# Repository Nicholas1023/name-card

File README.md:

# My PCB Name Card
My PCB name card has a microcontroller that lights 2 LEDs as it's output. It also has wireless capabilities on it. The card uses a 3V CR2032 battery to power it.

## Schematic

## PCB

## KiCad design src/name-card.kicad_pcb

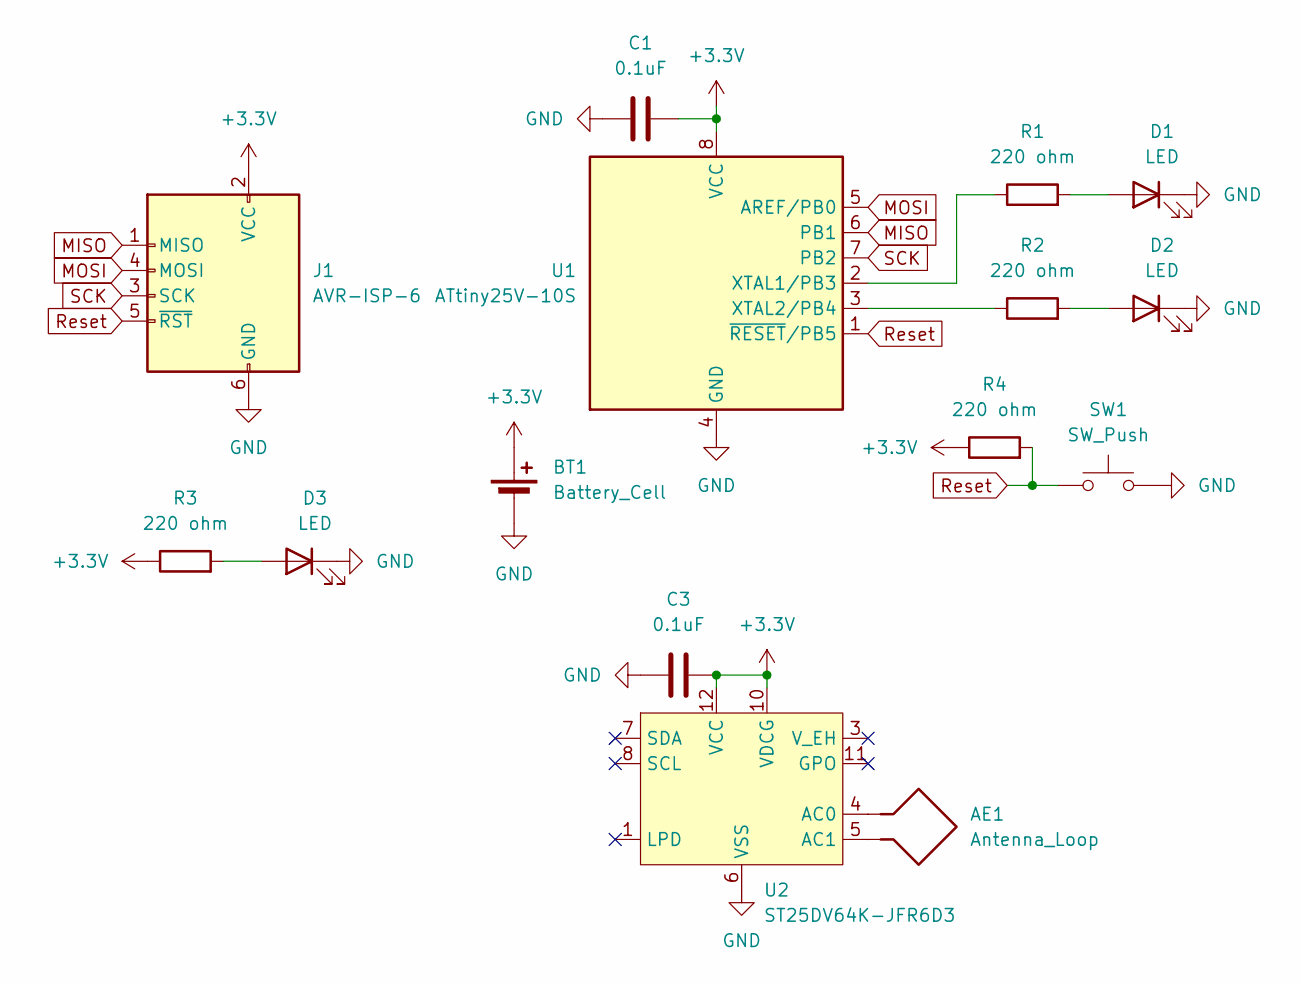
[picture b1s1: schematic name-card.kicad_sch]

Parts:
AE1: Antenna_Loop; NFC Coil
BT1: Battery_Cell; BatteryHolder_Keystone_3034_1x20mm
C1, C3: 0.1uF; C_0402_1005Metric; LCSC C1581
D1, D2, D3: LED; LED_0603_1608Metric; LCSC C2286
J1: AVR-ISP-6; PinHeader_2x03_P2.54mm_Vertical
R1, R2, R3, R4: 220 ohm; R_0402_1005Metric; LCSC C25091
SW1: SW_Push; SW_PUSH_6mm
U1: ATtiny25V-10S; SOIC-8_5.3x5.3mm_P1.27mm; LCSC C139660
U2: ST25DV64K-JFR6D3; ST_UFDFPN-12-1EP_3x3mm_P0.5mm_EP1.4x2.55mm; LCSC C5267460

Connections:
+3.3V: BT1.1 (+), C1.1, C3.1, J1.2 (VCC), R3.1, R4.1, U1.8 (VCC), U2.10 (VDCG), U2.12 (VCC)
GND: BT1.2 (-), C1.2, C3.2, D1.1 (K), D2.1 (K), D3.1 (K), J1.6 (GND), SW1.2, U1.4 (GND), U2.6 (VSS)
MISO: J1.1 (MISO), U1.6 (PB1)
MOSI: J1.4 (MOSI), U1.5 (AREF/PB0)
unnamed: D1.2 (A), R1.2
unnamed: D2.2 (A), R2.2
unnamed: D3.2 (A), R3.2
unnamed: R1.1, U1.2 (XTAL1/PB3)
unnamed: R2.1, U1.3 (XTAL2/PB4)
unnamed: AE1.1, U2.4 (AC0)
unnamed: AE1.2, U2.5 (AC1)
Reset: J1.5 (~RST), R4.2, SW1.1, U1.1 (~RESET/PB5)
SCK: J1.3 (SCK), U1.7 (PB2)

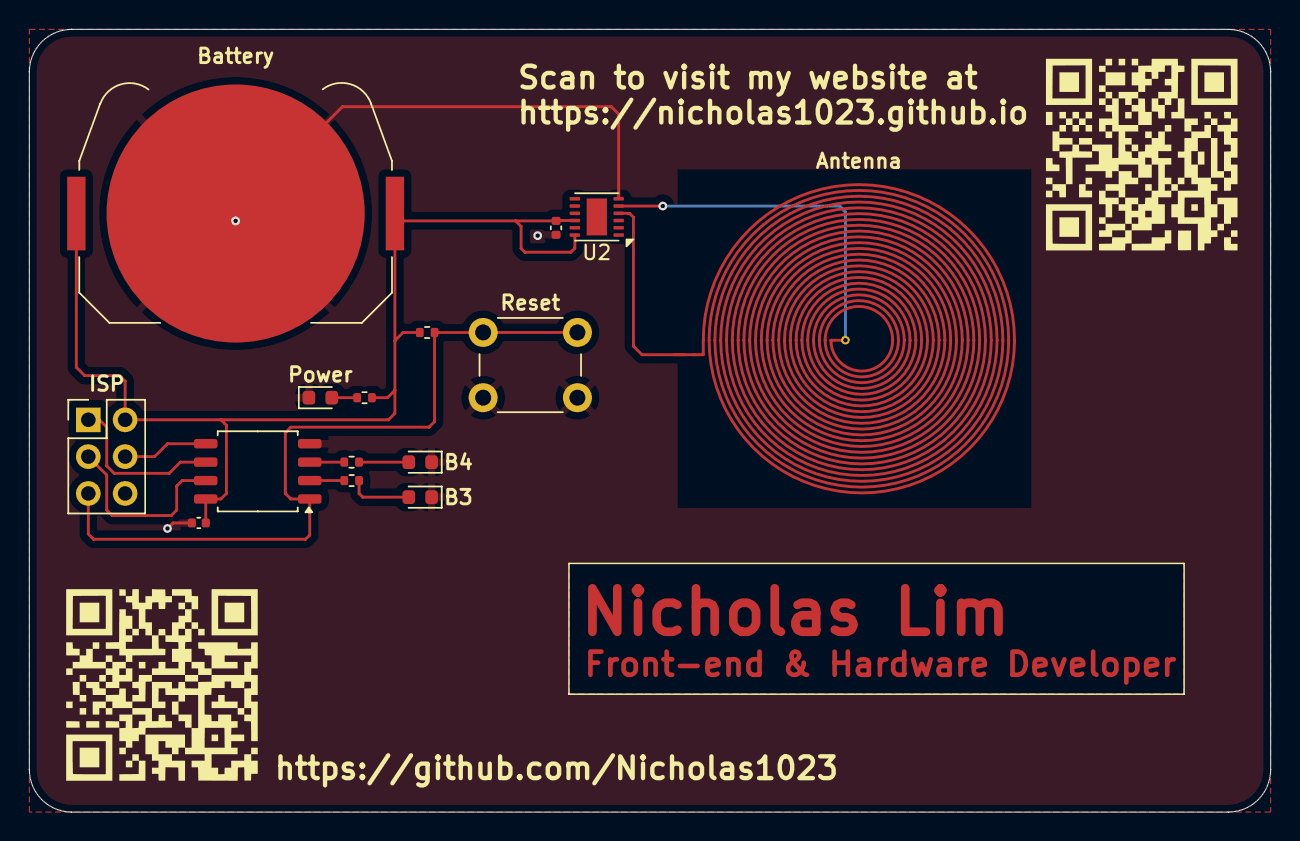
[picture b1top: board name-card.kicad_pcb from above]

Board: 2 copper layers, 85.6 x 54.0 mm, 15 parts (0 on the bottom side), 13 nets.

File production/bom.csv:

Designator,Footprint,Quantity,Value,LCSC Part #
"C1, C3",0402,2,0.1uF,C1581
"D1, D2, D3",0603,3,LED,C2286
J1,PinHeader_2x03_P2.54mm_Vertical,1,AVR-ISP-6,C65114
"R1, R2, R3, R4",0402,4,220 ohm,C25091
U1,SOIC-8_5.3x5.3mm_P1.27mm,1,ATtiny25V-10S,C139660
U2,ST_UFDFPN-12-1EP_3x3mm_P0.5mm_EP1.4x2.55mm,1,ST25DV64K-JFR6D3,C5267460

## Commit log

2025-08-23 Add schematics
2025-08-25 Add PCB
